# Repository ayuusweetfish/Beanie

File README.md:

# Beanie the Snail

Submission to [IOCCC29](https://www.ioccc.org/). See [**prog.c**](./prog.c) for the code, and [**remarks.md**](./remarks.md) for the comments.

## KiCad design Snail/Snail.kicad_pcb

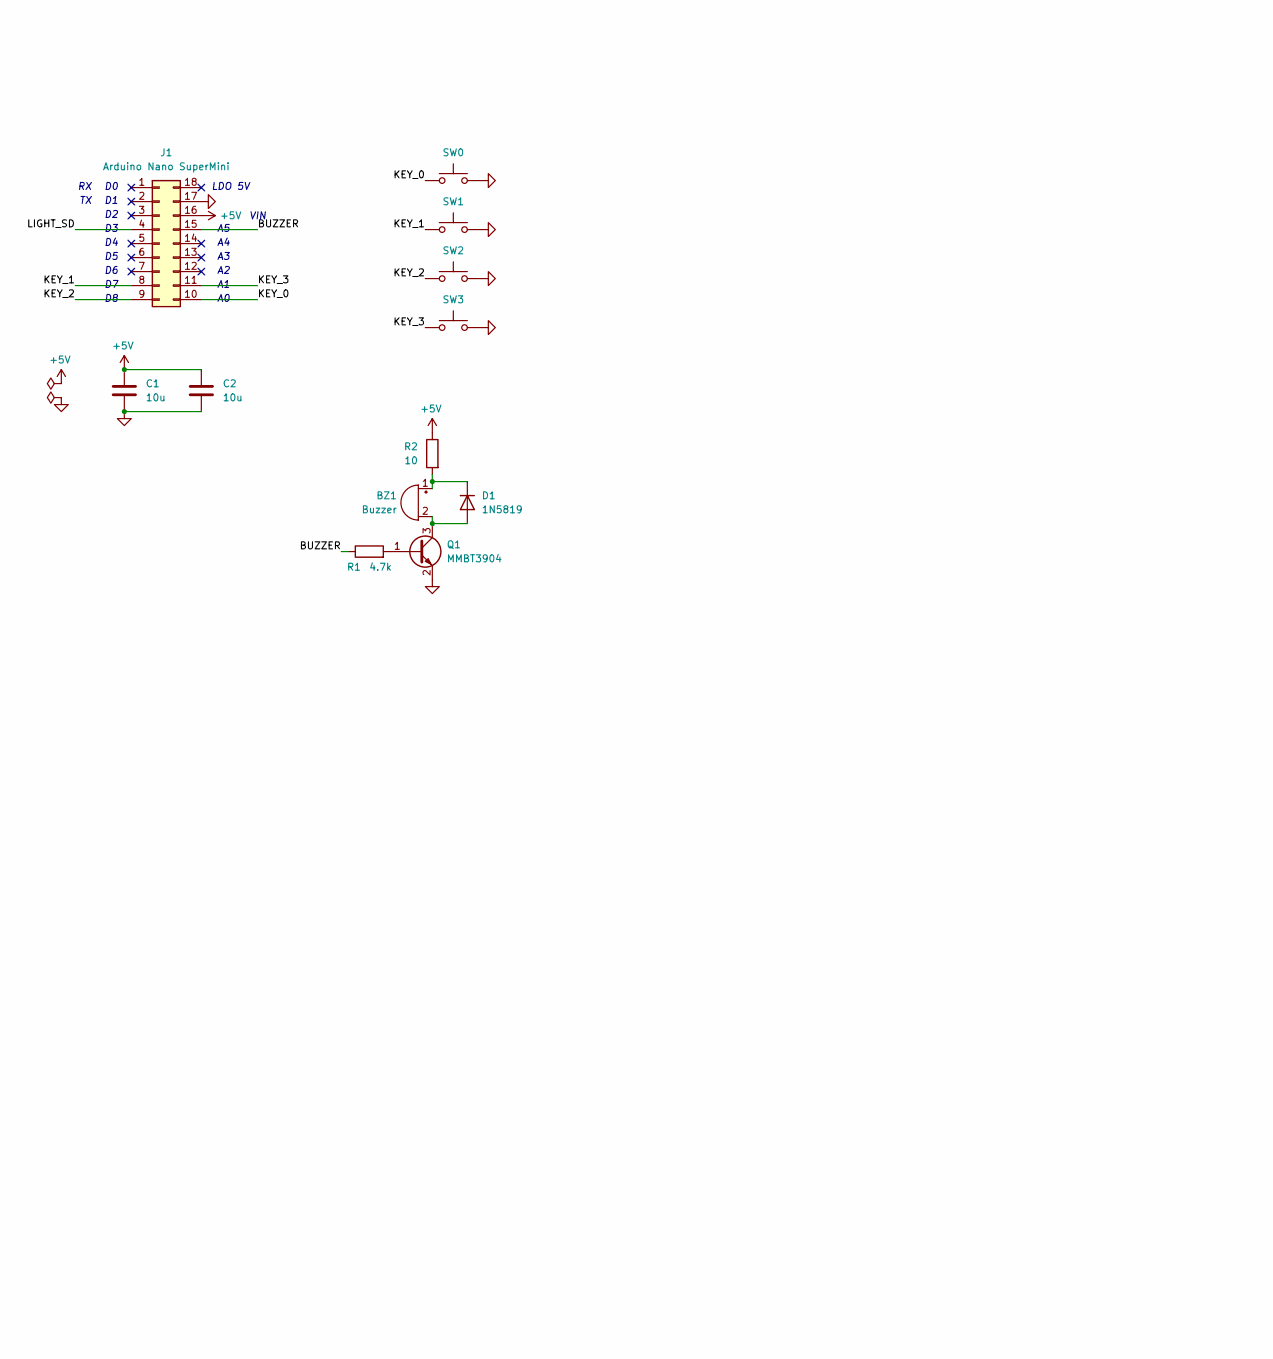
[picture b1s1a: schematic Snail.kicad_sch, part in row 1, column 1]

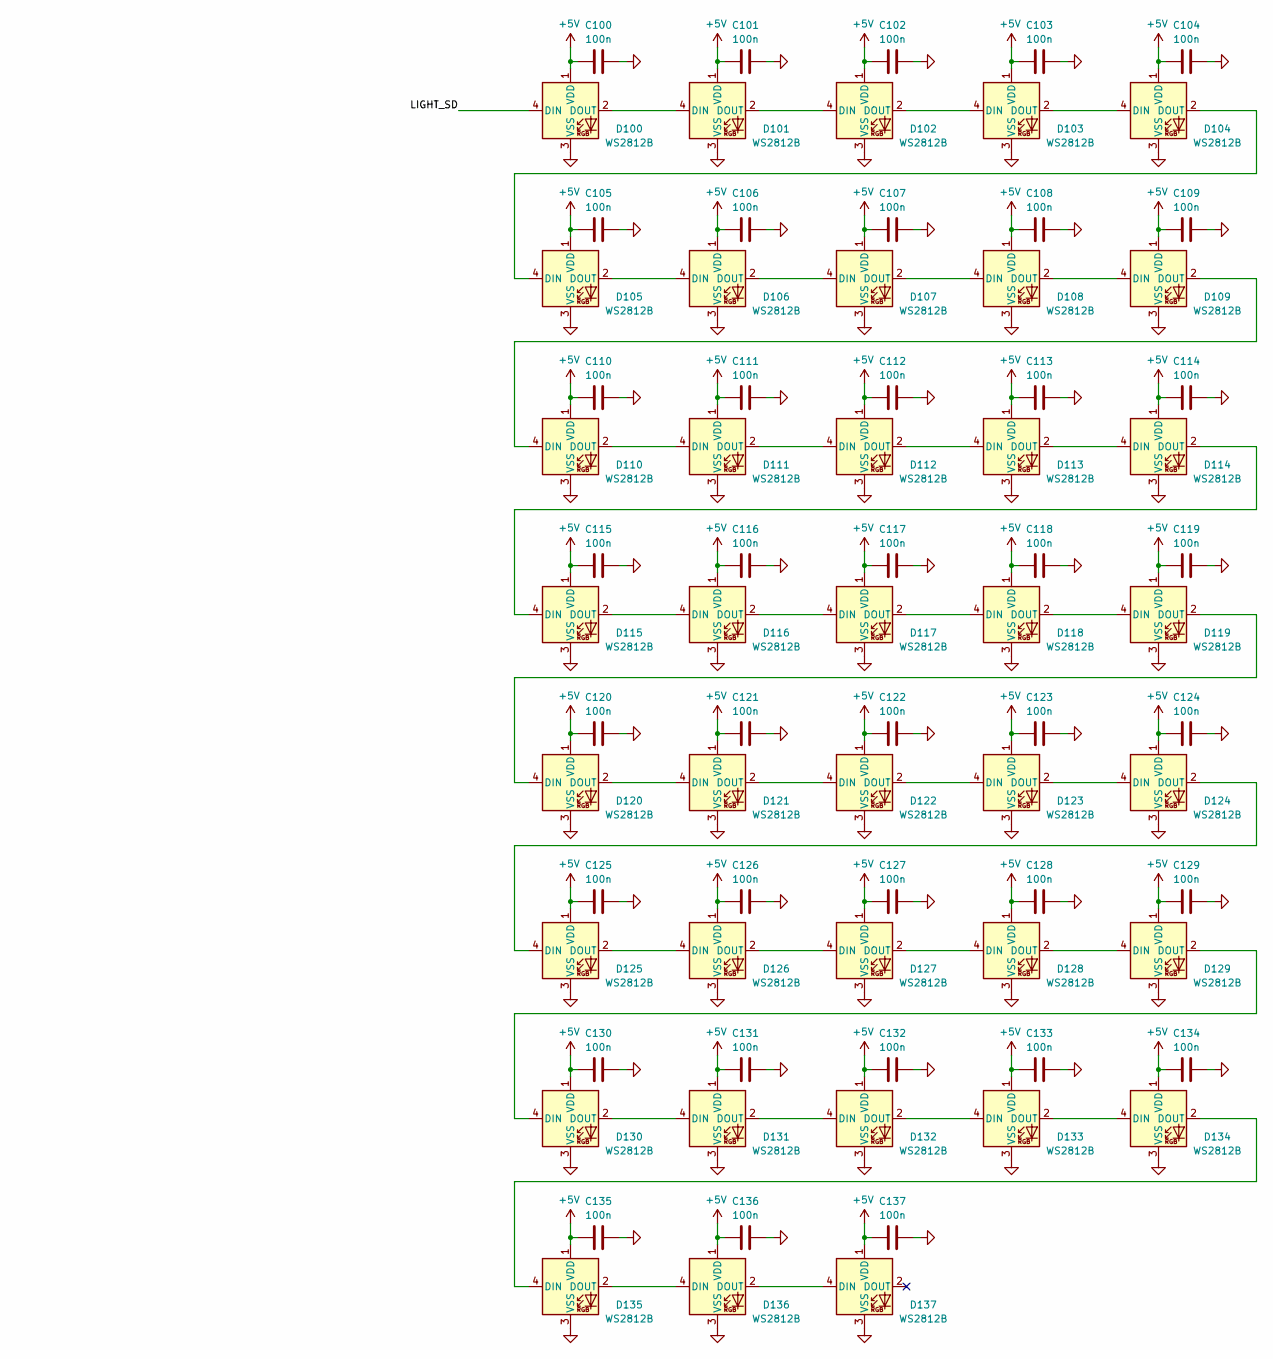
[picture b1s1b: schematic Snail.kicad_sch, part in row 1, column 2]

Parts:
BZ1: Buzzer; MagneticBuzzer_StarMicronics_QMB-105
C1, C2: 10u; C_0603_1608Metric
C100, C101, C102, C103, C104, C105, C106, C107, C108, C109, C110, C111, C112, C113, C114, C115, C116, C117, C118, C119, C120, C121, C122, C123, C124, C125, C126, C127, C128, C129, C130, C131, C132, C133, C134, C135, C136, C137: 100n; C_0402_1005Metric
D1: 1N5819; D_SOD-323
D100, D101, D102, D103, D104, D105, D106, D107, D108, D109, D110, D111, D112, D113, D114, D115, D116, D117, D118, D119, D120, D121, D122, D123, D124, D125, D126, D127, D128, D129, D130, D131, D132, D133, D134: WS2812B; LED_ARGB_5050; LCSC PN C5349954
D135, D136, D137: WS2812B; LED_ARGB_3528; LCSC PN C5349954
J1: Arduino Nano SuperMini; DevBoard_SuperMini
Q1: MMBT3904; SOT-23
R1: 4.7k; R_0402_1005Metric
R2: 10; R_0402_1005Metric
SW0, SW1, SW2, SW3: SW_Push; SW_Push_1TS009xxxx-xxxx-xxxx_6x6x5mm

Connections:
+5V: C1.1, C2.1, C100.1, C101.1, C102.1, C103.1, C104.1, C105.1, C106.1, C107.1, C108.1, C109.1, C110.1, C111.1, C112.1, C113.1, C114.1, C115.1, C116.1, C117.1, C118.1, C119.1, C120.1, C121.1, C122.1, C123.1, C124.1, C125.1, C126.1, C127.1, C128.1, C129.1, C130.1, C131.1, C132.1, C133.1, C134.1, C135.1, C136.1, C137.1, D100.1 (VDD), D101.1 (VDD), D102.1 (VDD), D103.1 (VDD), D104.1 (VDD), D105.1 (VDD), D106.1 (VDD), D107.1 (VDD), D108.1 (VDD), D109.1 (VDD), D110.1 (VDD), D111.1 (VDD), D112.1 (VDD), D113.1 (VDD), D114.1 (VDD), D115.1 (VDD), D116.1 (VDD), D117.1 (VDD), D118.1 (VDD), D119.1 (VDD), D120.1 (VDD), D121.1 (VDD), D122.1 (VDD), D123.1 (VDD), D124.1 (VDD), D125.1 (VDD), D126.1 (VDD), D127.1 (VDD), D128.1 (VDD), D129.1 (VDD), D130.1 (VDD), D131.1 (VDD), D132.1 (VDD), D133.1 (VDD), D134.1 (VDD), D135.1 (VDD), D136.1 (VDD), D137.1 (VDD), J1.16, R2.1
/BUZZER: J1.15, R1.1
/KEY_0: J1.10, SW0.1
/KEY_1: J1.8, SW1.1
/KEY_2: J1.9, SW2.1
/KEY_3: J1.11, SW3.1
/LIGHT_SD: D100.4 (DIN), J1.4
GND: C1.2, C2.2, C100.2, C101.2, C102.2, C103.2, C104.2, C105.2, C106.2, C107.2, C108.2, C109.2, C110.2, C111.2, C112.2, C113.2, C114.2, C115.2, C116.2, C117.2, C118.2, C119.2, C120.2, C121.2, C122.2, C123.2, C124.2, C125.2, C126.2, C127.2, C128.2, C129.2, C130.2, C131.2, C132.2, C133.2, C134.2, C135.2, C136.2, C137.2, D100.3 (VSS), D101.3 (VSS), D102.3 (VSS), D103.3 (VSS), D104.3 (VSS), D105.3 (VSS), D106.3 (VSS), D107.3 (VSS), D108.3 (VSS), D109.3 (VSS), D110.3 (VSS), D111.3 (VSS), D112.3 (VSS), D113.3 (VSS), D114.3 (VSS), D115.3 (VSS), D116.3 (VSS), D117.3 (VSS), D118.3 (VSS), D119.3 (VSS), D120.3 (VSS), D121.3 (VSS), D122.3 (VSS), D123.3 (VSS), D124.3 (VSS), D125.3 (VSS), D126.3 (VSS), D127.3 (VSS), D128.3 (VSS), D129.3 (VSS), D130.3 (VSS), D131.3 (VSS), D132.3 (VSS), D133.3 (VSS), D134.3 (VSS), D135.3 (VSS), D136.3 (VSS), D137.3 (VSS), J1.17, Q1.2 (E), SW0.2, SW1.2, SW2.2, SW3.2
unnamed: BZ1.1 (+), D1.1 (K), R2.2
unnamed: BZ1.2 (-), D1.2 (A), Q1.3 (C)
unnamed: D100.2 (DOUT), D101.4 (DIN)
unnamed: D101.2 (DOUT), D102.4 (DIN)
unnamed: D102.2 (DOUT), D103.4 (DIN)
unnamed: D103.2 (DOUT), D104.4 (DIN)
unnamed: D104.2 (DOUT), D105.4 (DIN)
unnamed: D105.2 (DOUT), D106.4 (DIN)
unnamed: D106.2 (DOUT), D107.4 (DIN)
unnamed: D107.2 (DOUT), D108.4 (DIN)
unnamed: D108.2 (DOUT), D109.4 (DIN)
unnamed: D109.2 (DOUT), D110.4 (DIN)
unnamed: D110.2 (DOUT), D111.4 (DIN)
unnamed: D111.2 (DOUT), D112.4 (DIN)
unnamed: D112.2 (DOUT), D113.4 (DIN)
unnamed: D113.2 (DOUT), D114.4 (DIN)
unnamed: D114.2 (DOUT), D115.4 (DIN)
unnamed: D115.2 (DOUT), D116.4 (DIN)
unnamed: D116.2 (DOUT), D117.4 (DIN)
unnamed: D117.2 (DOUT), D118.4 (DIN)
unnamed: D118.2 (DOUT), D119.4 (DIN)
unnamed: D119.2 (DOUT), D120.4 (DIN)
unnamed: D120.2 (DOUT), D121.4 (DIN)
unnamed: D121.2 (DOUT), D122.4 (DIN)
unnamed: D122.2 (DOUT), D123.4 (DIN)
unnamed: D123.2 (DOUT), D124.4 (DIN)
unnamed: D124.2 (DOUT), D125.4 (DIN)
unnamed: D125.2 (DOUT), D126.4 (DIN)
unnamed: D126.2 (DOUT), D127.4 (DIN)
unnamed: D127.2 (DOUT), D128.4 (DIN)
unnamed: D128.2 (DOUT), D129.4 (DIN)
unnamed: D129.2 (DOUT), D130.4 (DIN)
unnamed: D130.2 (DOUT), D131.4 (DIN)
unnamed: D131.2 (DOUT), D132.4 (DIN)
unnamed: D132.2 (DOUT), D133.4 (DIN)
unnamed: D133.2 (DOUT), D134.4 (DIN)
unnamed: D134.2 (DOUT), D135.4 (DIN)
unnamed: D135.2 (DOUT), D136.4 (DIN)
unnamed: D136.2 (DOUT), D137.4 (DIN)
unnamed: Q1.1 (B), R1.2

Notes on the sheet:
VIN
LDO 5V

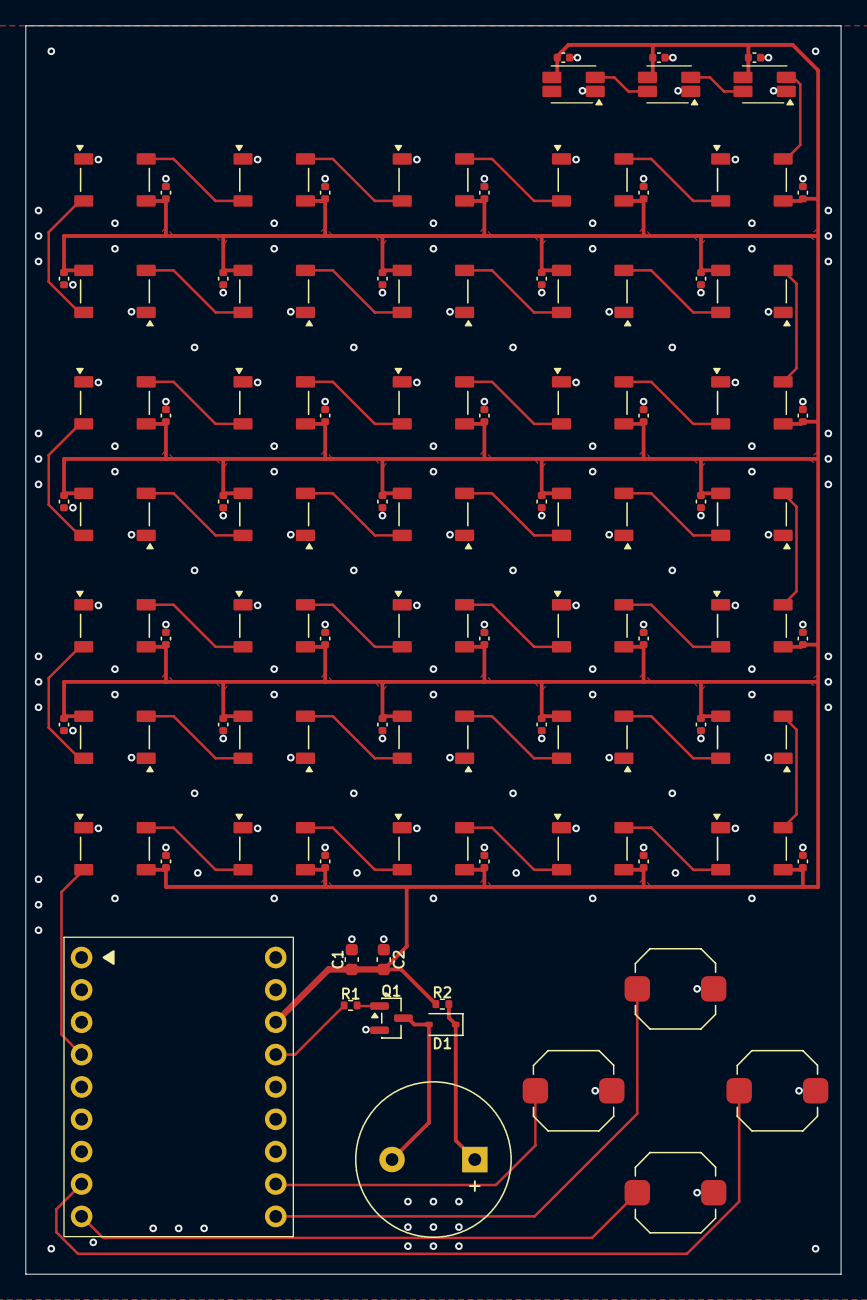
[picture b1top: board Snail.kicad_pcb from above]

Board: 2 copper layers, 64.0 x 98.0 mm, 88 parts (0 on the bottom side), 48 nets.

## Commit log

2025-03-15 Rolling with almost working game logic 🎉
2025-03-15 Get smarter (⌐■֊■)
2025-03-15 Use ncurses
2025-03-15 Prevent out-of-bound moves
2025-03-15 Migrate from ncurses to ANSI control sequences
2025-03-15 🚧 Twisted key handling...
2025-03-15 Less bytes
2025-03-15 Moving with keys 💃
2025-03-15 Try to get a bit smarter > <
2025-03-15 Randomly roll with random strategies?
2025-03-15 Trying to get a bit smarter?
2025-03-15 🚧 Random? Probably need to get more flexible
2025-03-16 More adversarial with non-standard cases
2025-03-16 Revise adversary logic
2025-03-16 Simplify logic (less bytes)
2025-03-16 Less bytes (both in code and memory)
2025-03-16 Fix row's monster missing
    Move 2
    3 3 3 3 3
    1 1 1 1 [0]
    0 0 0 1 0
    1 1 1 2 1
    0 0 0 1 0
2025-03-16 Infer monsters to avoid all cases of missing monsters
2025-03-16 Unify adversarial cases
2025-03-16 Further unify
2025-03-16 Fix chained inferences
    Move 1
    3 3 3 3 3
    1 1 1 1 0
    [2] 1 1 1 1
    1 0 0 0 0
    1 0 0 0 0
2025-03-16 Fixes per warnings
2025-03-16 Less bytes? Further obfuscation
2025-03-16 Compact!
2025-03-16 Various revisions
    Mostly "less bytes"...?
2025-03-16 Further obfuscate
2025-03-16 Use one-dimensional array for less bytes
2025-03-16 Fill a few holes
    Is 2-move win possible now?
2025-03-16 Remove redundant check
2025-03-16 Display (O O) on monster encounter
2025-03-16 Commentary
2025-03-17 Pipe audio to SoX
2025-03-17 Pipe audio to a user-supplied destination
2025-03-20 Bug fix and more randomness
2025-03-21 Obfuscate, compactify, fix bug
2025-03-24 Add puzzle?
2025-03-24 Better random (?)
2025-03-24 Fuzz with LLVM libFuzzer
    Failure case: ASqMAAAAALa2tgAvtraMjAAAAAABjIyMAQD3dy8=
2025-03-24 Almost eliminate 2-step wins
    Failure case: 03uTbBgqAAAKfmxALUDMCkhICmwYKgAACgAKSEgKbBgqAAAACn5sQAolAApISApsGCoAAAoACkDMCkhICmwYqgAACgAKSEgKbBgqAAAAKgBISApsGCoACAoAAS7/AAAKSEgKbBgqAAAKAApISApsGCoAAAAKu2xALUDMCkhICmwYKgAACgAKSEgKb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
2025-03-24 Attempt to further eliminate 2-step wins
    Failure case: AAAAAAABAgIAAAAA3wAO////ANAAAAAAQQA=
2025-03-24 Better organized fuzz target
2025-03-24 Further obfuscate and less bytes
2025-03-24 Eliminate undefined behaviour and fix incorrect behaviour
2025-03-27 A fix and less bytes
2025-03-27 Further obfuscate and fewer (!) bytes
2025-03-27 Fix incorrect obfuscation, re-fuzz
2025-04-01 Further obfuscate
    +fuzz
2025-04-01 Further obfuscate and less bytes
    Failure case: ABQAAAABDs1WfjT5ZkBmQJws/2TLwmPL9E1kCzQ07AABQBYAAA==
2025-04-01 Fix undefined behaviour and further obfuscate
2025-04-01 Less bytes and further obfuscate
2026-02-19 Fix incorrect behaviour with `char` defaulting to unsigned
2026-02-20 Fix out-of-bound access
2026-02-20 Update fuzzer
2026-02-20 Accept 2-round wins in fuzze (> -)
2026-02-20 Fix uninitialized stack variable access > <
2026-02-20 h = 'h'
2026-02-27 Peephole
2026-02-27 Add empty KiCad project
2026-02-27 Board configuration
2026-02-28 🚧 Schematic, lights TO-DO
2026-02-28 Full schematic & footprints
2026-02-28 Lay out one row
2026-02-28 Lay out LED matrix
2026-03-01 🚧 All components layout
2026-03-01 Finish layout & routing
2026-03-01 Revise board design for rounded tracks & teardrops
2026-03-01 Add stitching vias
2026-03-02 Finalize by silkscreen
2026-03-07 fw: Add LED strip testrun
2026-03-07 fw: Buzzer and buttons!
2026-03-07 fw: Test all four buttons
2026-03-07 fw: All 38 lights ✨
2026-03-07 hw: Update files with actual mounted component value
2026-03-10 Many peephole obfuscations
2026-03-10 Return move result in move subroutine
2026-03-10 More obfuscation & minimization > <
2026-03-10 Fix fuzz program
2026-03-10 Keep last player position at win
2026-03-10 Reorganize console printing subroutines
2026-03-10 Revise audio support; use square waves
2026-03-10 Sounds 🔔
2026-03-11 Eliminate UB
2026-03-11 Peephole obfuscation
2026-03-11 Switch LCG
2026-03-11 Some mind-bending puzzle
2026-03-11 Add notes
2026-03-11 Change character display
2026-03-11 Keep row position at failure
2026-03-11 Readjust 2-step wins
2026-03-11 Revert change due to potential bug (missing an object!)
2026-03-11 Reorder problems
2026-03-11 Fix empty row bug
2026-03-11 Handle 2x2 square corner case; passing no-empty-row test
2026-03-11 Further obfuscation
2026-03-11 Fix sound
2026-03-11 Optimize sound
2026-03-11 Polynomial interpolation
2026-03-11 Further obfuscate and compact-ify
2026-03-11 Integrate beep subroutine into `main()`
2026-03-11 Misleading ^ ^
2026-03-11 Update fuzzing program
2026-03-11 Further obfuscate, rename variables ^ ^
2026-03-12 Prepare for `mkiocccentry`
2026-03-12 Reorganize files
2026-03-12 Move answer files to `misc/`
2026-03-12 Add `mkiocccentry` command line to notes
2026-03-12 Move build command to dedicated shell script
2026-03-12 Edit Makefile from example
2026-03-12 Check-in example try.sh
2026-03-12 Edit try.sh from example
2026-03-12 Press q/^C/^D to quit
2026-03-12 Bye-bye emoticon
2026-03-12 Fix compiler warnings
2026-03-12 Peephole & fuzz
2026-03-12 Eliminate an obvious (not-very-obfuscated) `if`
2026-03-12 New operators ^ ^
2026-03-13 Less warnings
2026-03-13 Fewer warnings, again
2026-03-13 Even fewer warnings
2026-03-13 Minor audio fix-up
2026-03-13 Eliminate warnings when `char` is signed
2026-03-13 Fix logic error regression
2026-03-13 Strange words (^ -)
2026-03-13 Stranger long words
2026-03-13 Refactor for embedded integration (1/n)
2026-03-13 Refactor for embedded integration (2/n)
2026-03-13 Refactor for embedded integration (3/n)
2026-03-13 Refactor for embedded integration (4/n)
2026-03-13 Fix incorrect audio at bye-bye
2026-03-13 Correctly running on Arduino!
2026-03-13 Check in Arduino program
2026-03-13 Fix restarting on Arduino
2026-03-13 Remove copy and place symlink
2026-03-13 More entropy in Arduino
2026-03-13 Add button support in Arduino
2026-03-13 Add fuzz target to Makefile
2026-03-13 (WIP) Remarks
2026-03-13 Fix fuzzing not reproducible, dependent on previous runs
2026-03-13 Finish remarks
2026-03-14 Add new Arduino sketch; migrate to `arduino-cli`
2026-03-14 Non-blocking debouncing
2026-03-14 Fix conflicting buttons
2026-03-14 Finish game on Arduino
2026-03-14 Wait for a button input after each trap
2026-03-14 (WIP) Arduino update
2026-03-14 Revert "Wait for a button input after each trap"
    This reverts commit 8e8f817b72ec0706a30fd985d8881b6ef8183709.
2026-03-15 Minor revision
2026-03-15 Show newly marked free cells after trap
2026-03-15 Test mark behaviour in fuzzer
2026-03-15 Update Arduino port, adding trap animation
2026-03-15 Fix Arduino trap SFX delay
2026-03-15 Fix broken core logic
2026-03-15 Mark newly unrevealed traps
2026-03-15 Beep at new game
2026-03-15 Minor revisions
    GCC 15.2.1 reports a false positive at `-O3` (`-Warray-bounds=1`) at prog.c:48
2026-03-15 Handle 2-move wins on Arduino
2026-03-15 Further minify & obfuscate
2026-03-16 Reorganize directories; revise documentation
2026-03-16 Add missing link to `prog.c`
2026-03-16 Break lines at 100 columns
2026-03-16 Eliminate zeros from core game logic
2026-03-16 Document absence of zero
2026-03-16 Fix incorrect behaviour with signed `char`
2026-03-16 Fix compiler warning with signed `char`
2026-03-16 Documentation revisions
